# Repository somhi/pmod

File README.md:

# PMOD / USB3 adapters

This repository is home of simple adapters between PMOD / USB3 and other connectors.

* PMOD-USB3 is a passive adapter between PMOD and USB3 (see SNAC adapters used in MiSTer project).
* PS2-UART-USB3 is a passive adapter between USB3 and PS2 connector (mouse+keyboard). It also offers an UART header (Rx/Tx).

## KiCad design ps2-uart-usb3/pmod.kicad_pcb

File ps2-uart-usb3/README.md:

# USB3 to PS2/UART adapter

PS2-UART-USB3 is a passive adapter between USB3 and PS2 connector (mouse+keyboard). It also offers an UART header (Rx/Tx/GND). 

**STATUS**: working Ok. See testing and improvement notes below.

See correspondence of pins in [schematic](pmod.pdf). 

PS2 connector has all signal pins connected so a splitter cable can be used to connect a PS2 keyboard and mouse.

JP1 header is for selecting power supply of PS2 connector. Three options are possible:

* 5V: Place a jumper between VBUS and central pin
* External power supply can also be connected to the central pin and GND.
* ~~3V3: Place a jumper between 3V3 and central pin. For this is required a MiSTer Analog IO version with a jumper that connects 3V3 to pin 9 of USB3~~.  [CAUTION: this is not possible when using a male male USB3 cable as the pin 9 is connected to pin 5 at the other end of cable]

**NOTES ABOUT USB3 CABLES**

* male male cable is crossover cable, meaning that Rx- is connected to Tx- and Rx+ to Tx+

* female male cable is straight cable, meaning all pins have exact correspondence in each side of cable (Rx- with Rx-, ...)

**SETUP IN MISTER DE10-nano FPGA**

* Connect  an [SNAC level shifter adapter](https://manuferhi.com/p/snac-adapter-for-mister) to the user IO port of MiSTer Analog addon

* Connect a male male USB3 cable between the SNAC adapter and the USB3 to PS2 adapter

* Connect a [PS2 splitter cable](https://es.aliexpress.com/item/32827138560.html) if you intend to use keyboard and mouse simultaneously.

**TODO & IMPROVEMENTS**

* Make a male USB3 version with voltage protections so the SNAC adapter and male male cable would be unnecessary
* Shield pins of PS2 connector are not connected to GND
* 3V3 silkscreen NOTE at pcb back "3V3 from MiSTer analog IO with user IO jumper placed"

**TESTING**

* Tested using PMOD-USB3 adapter: UART, keyboard and mouse works well, with 3V3 without SNAC adapter, or with 5V and SNAC level shifter adapter.  This means in MiSTer should work.

  NOTE: Code in FPGA side need to take into account the crossover signals of the male to male cable.

* Tested from USB3 port of Deca cape: Keyboard not working good with the integrated level shifter of Deca cape.

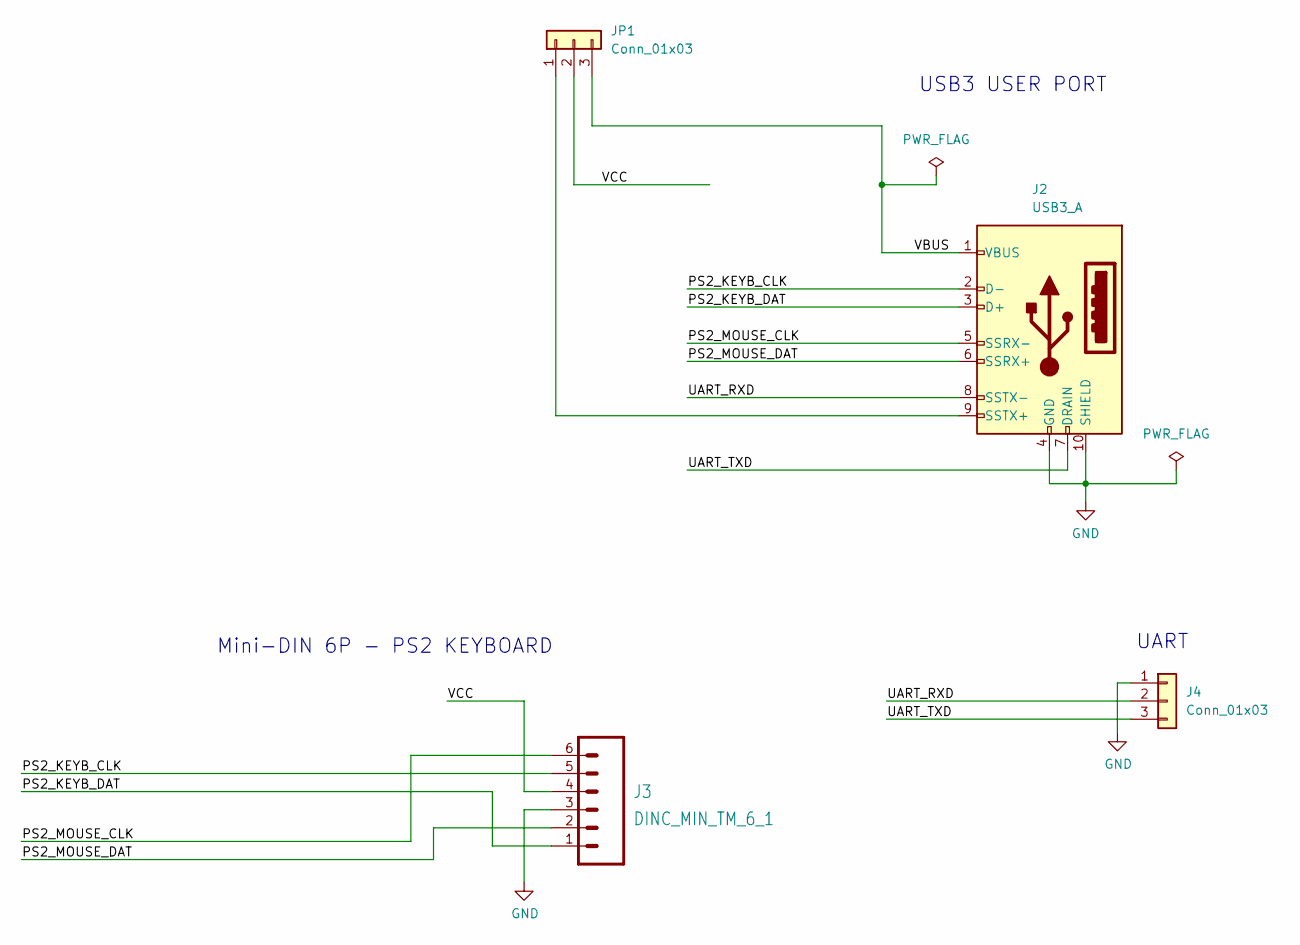
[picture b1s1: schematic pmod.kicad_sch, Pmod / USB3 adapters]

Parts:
J2: USB3_A; USB-3.0-TH_C69073
J3: DINC_MIN_TM_6_1; DINC_MIN_TM_6_1PRIMARY
J4: Conn_01x03; PinHeader_1x03_P2.54mm_Vertical
JP1: Conn_01x03; PinHeader_1x03_P2.54mm_Vertical

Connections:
/PS2_KEYB_CLK: J2.2 (D-), J3.5
/PS2_KEYB_DAT: J2.3 (D+), J3.1
/PS2_MOUSE_CLK: J2.5 (SSRX-), J3.6
/PS2_MOUSE_DAT: J2.6 (SSRX+), J3.2
/UART_RXD: J2.8 (SSTX-), J4.2
/UART_TXD: J2.7 (DRAIN), J4.3
/VBUS: J2.1 (VBUS), JP1.3
/VCC: J3.4, JP1.2
GND: J2.4 (GND), J2.10 (SHIELD), J3.3, J4.1
unnamed: J2.9 (SSTX+), JP1.1

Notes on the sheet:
UART
Mini-DIN 6P - PS2 KEYBOARD
USB3 USER PORT

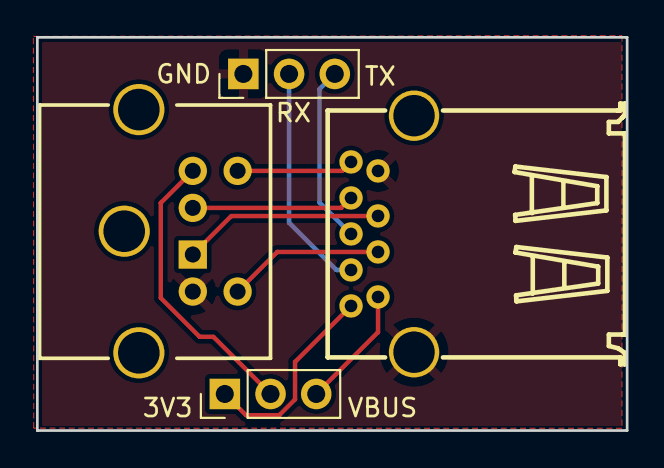
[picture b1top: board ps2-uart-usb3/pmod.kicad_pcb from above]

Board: 2 copper layers, 32.8 x 21.8 mm, 4 parts (0 on the bottom side), 10 nets.

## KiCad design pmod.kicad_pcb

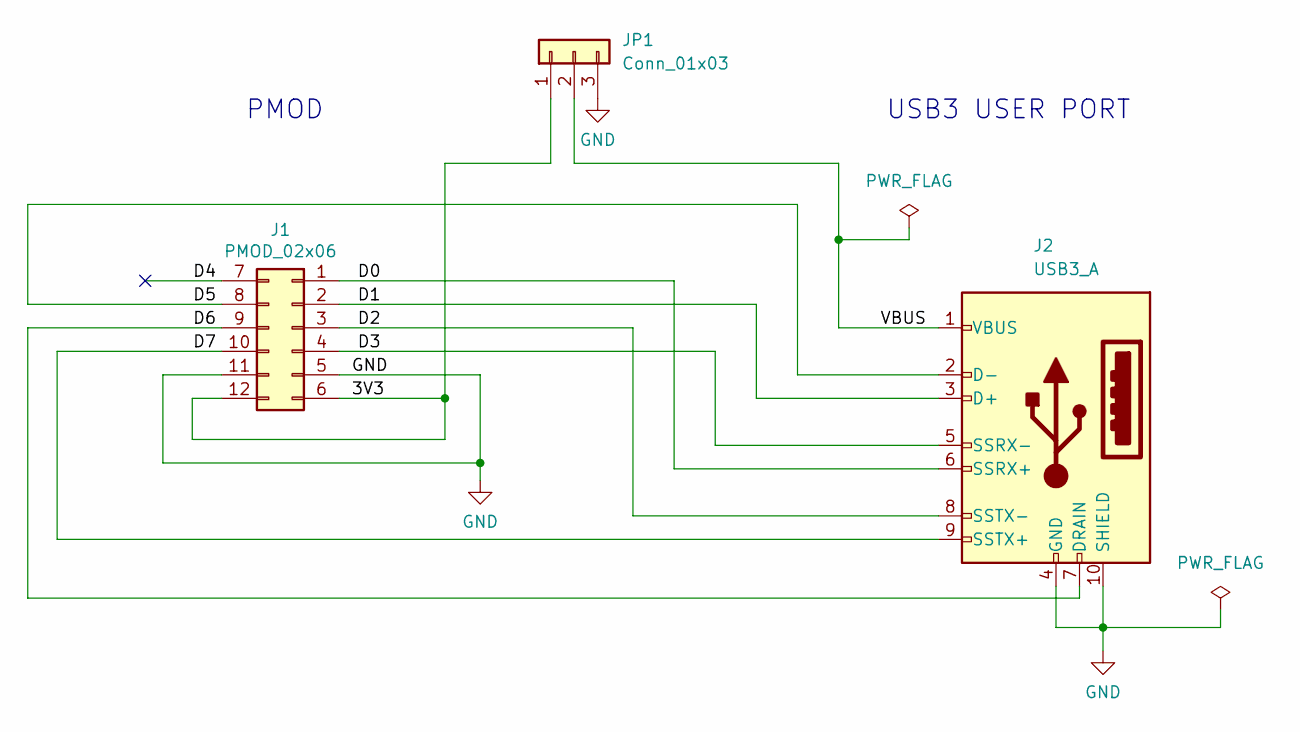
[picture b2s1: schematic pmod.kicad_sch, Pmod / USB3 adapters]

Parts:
J1: PMOD_02x06; PMODHeader_2x06_P2.54mm_Horizontal
J2: USB3_A; USB-3.0-TH_C69073
JP1: Conn_01x03; PinHeader_1x03_P2.54mm_Vertical

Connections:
/3V3: J1.6, J1.12, JP1.1
/D0: J1.1, J2.6 (SSRX+)
/D1: J1.2, J2.3 (D+)
/D2: J1.3, J2.8 (SSTX-)
/D3: J1.4, J2.5 (SSRX-)
/D4: J1.7
/D5: J1.8, J2.2 (D-)
/D6: J1.9, J2.7 (DRAIN)
/D7: J1.10, J2.9 (SSTX+)
/VBUS: J2.1 (VBUS), JP1.2
GND: J1.5, J1.11, J2.4 (GND), J2.10 (SHIELD), JP1.3

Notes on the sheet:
PMOD
USB3 USER PORT

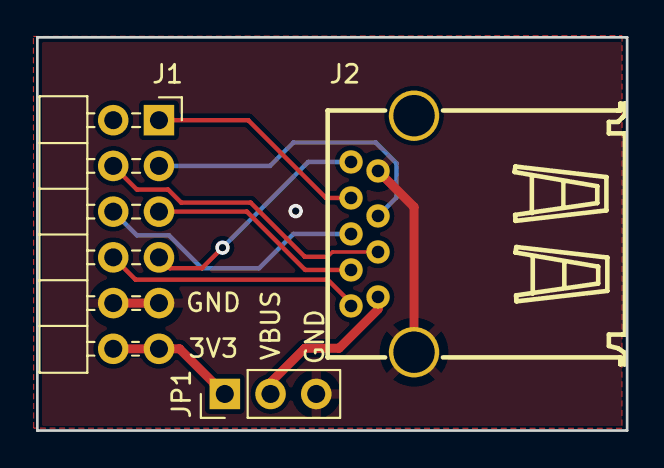
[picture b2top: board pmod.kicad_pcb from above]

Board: 2 copper layers, 32.8 x 21.8 mm, 3 parts (0 on the bottom side), 10 nets.

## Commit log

2023-03-17 added ps2-uart-usb3 module
2023-04-02 updated readmes
2023-04-02 updated Readmes after testing

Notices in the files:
pmod-usb3/pmod.kicad_sch:
License: CC-BY-SA 4.0
